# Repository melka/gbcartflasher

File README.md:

# gbcartflasher

PCB for the ATMega8515 / FT232RL based Gameboy Cart Flasher &amp; some mods to make it work easily under MacOS

## background

We needed to write a small text-based game, like Zork, for the gameboy. We wanted it to run on the original hardware and look like an original cartridge.

In order to flash a cartridge, you need to either mod an existing one by removing the ROM and replacing it with your own flash, but since the software was pretty simple, I figured I should make a PCB for a 32K flash that could be assembled easily. We had to make around 10 copies in a limited time.

One of the simplest and most used Gameboy Cart Flasher is the one designed by Kraku & Chroost. The schematics and software can be found on the [awesome website](http://www.reinerziegler.de/readplus.htm) maintained by Reiner Ziegler.

What you'll find in this repo are the eagle files ready to be sent to a fab house (I used [elecrow](https://www.elecrow.com/pcb-prototyping.html)), plus some instructions and a modified software to make it run easily on MacOS.

## BOM

Full BOM can be found on Mouser :
* [32K Cart](http://www.mouser.com/ProjectManager/ProjectDetail.aspx?AccessID=d0bee9d82e)
* [Cart Flasher](http://www.mouser.com/ProjectManager/ProjectDetail.aspx?AccessID=779e8e7766)
* [GB Connector](http://www.dx.com/p/repair-parts-replacement-gba-game-cart-slot-for-nds-lite-37787)

## notes on PCBs

The Gameboy Cartridge connector can be taken from a broken gameboy, but the easiest way to get one is to buy a Nintendo DS GBA Slot connector and [cutting some little plastic tabs](http://sudomod.com/old_forums/reply/771/) in order to get the original GB cartridges to fit.

In order to fit, the PCB for the cartridge needs to be 0.8mm thick, so be careful when ordering to check that your fab house can make it.

## programming the flasher

To program the ATmega8515, you'll need an ICSP programmer for AVR chips. I used an [USBasp](http://www.fischl.de/usbasp/) clone.

Using avrdude, fuses need to be set as low 0x1F and high 0xc9

```
avrdude -P usb -c usbasp -p ATmega8515 -qq -B 8 -U lfuse:w:0x1f:m -U hfuse:w:0xc9:m
````

I programmed my flasher using the .hex file [found here](http://www.reinerziegler.de/readplus.htm#GB_Flasher). Be careful to flash the USB version.

```
avrdude -P usb -c usbasp -p ATmega8515 -qq -B 8 -U flash:w:gbcf-fw-2.1-usb.hex
```

The firmware has been [rewritten in C in 2015 by Tauwasser](https://github.com/Tauwasser/GBCartFlasher), but I haven't tested that version personally.

## libftdi, kext and MacOS

On MacOS, when you plug the flasher, the OS loads one or more kexts to act as drivers for the hardware. Those kexts are AppleUSBFTDI and, if you installed the FTDI VCP drivers, FTDIUSBSerialDriver.kext.

The host software uses libftdi to talk to the flasher, and those kexts are locking the USB port we need.

An easy solution is to unload the kexts before launching the host software :

```
sudo kextunload /System/Library/Extensions/AppleUSBFTDI.kext/
sudo kextunload /System/Library/Extensions/FTDIUSBSerialDriver.kext/
sudo kextunload /Library/Extensions/FTDIUSBSerialDriver.kext/
```

But it's cumbersome, and I always forget that step...

Since kexts are loaded according to the USB VID / PID, we changed the VID / PID / Description of the FT232 chip using [FT_Prog](http://www.ftdichip.com/Support/Utilities.htm#FT_PROG) under Windows. Changing to those exacts values is required if you want to use the host software provided since they are hard-coded for the time being.

```
Product Description : gbcflsh
VID : 1209
PID : 6BCF
```

Those IDs are provided by the awesome [pid.codes project](http://pid.codes/).

By changing the IDs, MacOS no longer tries to load the AppleUSBFTDI & FTDIUSBSerialDriver kexts, and libftdi can do its work.

## host software

On mac, you'll need to install Qt4 & libftdi :

```
brew tap cartr/qt4
brew install cartr/qt4/qt libftdi
```

Then, in the gbcflsh_1.1_libftdi folder :

```
qmake && make
```

You should find a gbcflsh.app in the release folder.

### references
 * [jrodrigo gb cart flasher](http://www.jrodrigo.net/es/project/gameboy-cart-flasher/)

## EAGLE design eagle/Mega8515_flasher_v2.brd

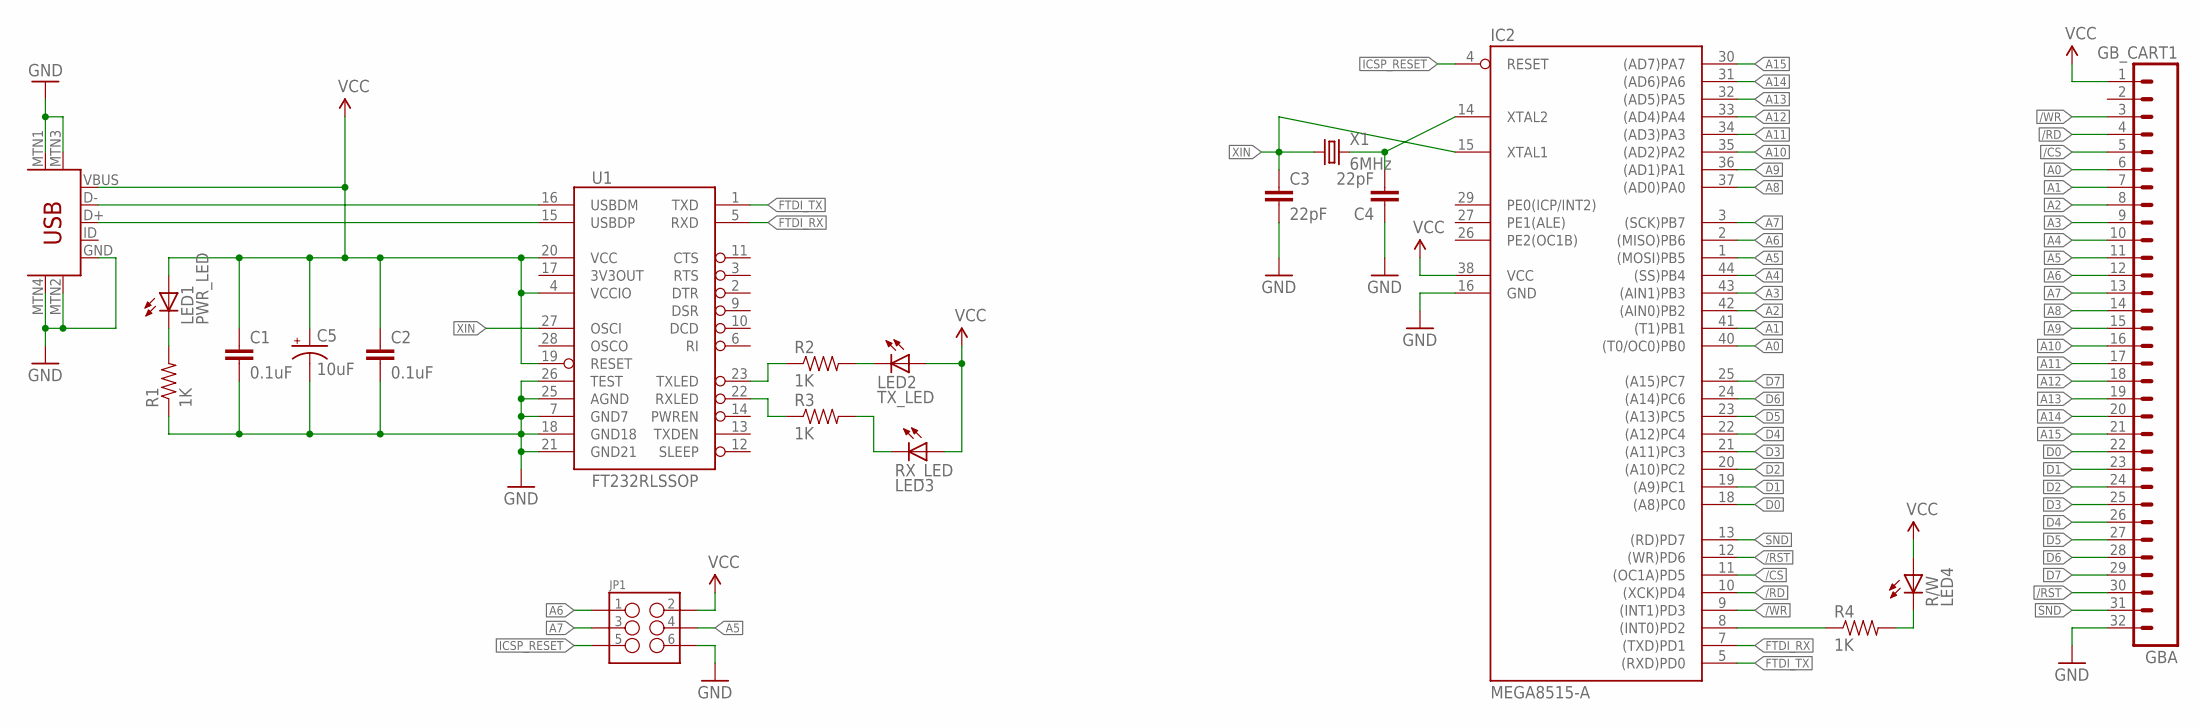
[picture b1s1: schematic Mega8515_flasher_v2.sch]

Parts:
C1, C2: 0.1uF; 1206
C3, C4: 22pF; 0805
C5: 10uF; EIA3216
GBA: GB_CART1; GB_CART_1
IC2: MEGA8515-A; TQFP44
JP1: SPARKFUN-CONNECTORS_M03X2SMT; SPARKFUN-CONNECTORS_2X3_SMT_POSTS
LED1: PWR_LED; LED-1206
LED2: TX_LED; LED-1206
R1, R2, R3, R4: 1K; 1206
R/W: LED4; LED-1206
RX_LED: LED3; LED-1206
U1: FT232RLSSOP; SSOP28DB
USB: USB-MINIB-5PIN; USB-MINIB
X1: 6MHz; SPARKFUN-FREQCTRL_CRYSTAL-SMD-11.8X5.5

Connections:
/CS: GBA.5, IC2.11 ((OC1A)PD5)
/RD: GBA.4, IC2.10 ((XCK)PD4)
/RST: GBA.30, IC2.12 ((WR)PD6)
/WR: GBA.3, IC2.9 ((INT1)PD3)
A0: GBA.6, IC2.40 ((T0/OC0)PB0)
A1: GBA.7, IC2.41 ((T1)PB1)
A2: GBA.8, IC2.42 ((AIN0)PB2)
A3: GBA.9, IC2.43 ((AIN1)PB3)
A4: GBA.10, IC2.44 ((SS)PB4)
A5: GBA.11, IC2.1 ((MOSI)PB5), JP1.4
A6: GBA.12, IC2.2 ((MISO)PB6), JP1.1
A7: GBA.13, IC2.3 ((SCK)PB7), JP1.3
A8: GBA.14, IC2.37 ((AD0)PA0)
A9: GBA.15, IC2.36 ((AD1)PA1)
A10: GBA.16, IC2.35 ((AD2)PA2)
A11: GBA.17, IC2.34 ((AD3)PA3)
A12: GBA.18, IC2.33 ((AD4)PA4)
A13: GBA.19, IC2.32 ((AD5)PA5)
A14: GBA.20, IC2.31 ((AD6)PA6)
A15: GBA.21, IC2.30 ((AD7)PA7)
D0: GBA.22, IC2.18 ((A8)PC0)
D1: GBA.23, IC2.19 ((A9)PC1)
D2: GBA.24, IC2.20 ((A10)PC2)
D3: GBA.25, IC2.21 ((A11)PC3)
D4: GBA.26, IC2.22 ((A12)PC4)
D5: GBA.27, IC2.23 ((A13)PC5)
D6: GBA.28, IC2.24 ((A14)PC6)
D7: GBA.29, IC2.25 ((A15)PC7)
FTDI_RX: IC2.7 ((TXD)PD1), U1.5 (RXD)
FTDI_TX: IC2.5 ((RXD)PD0), U1.1 (TXD)
GND: C1.2, C2.2, C3.2, C4.1, C5.C (-), GBA.32, IC2.16 (GND), JP1.6, R1.1, U1.7 (GND7), U1.18 (GND18), U1.21 (GND21), U1.25 (AGND), U1.26 (TEST), USB.GND, USB.MTN1 (MTN2), USB.MTN2 (MTN3), USB.MTN3 (MTN1), USB.MTN4
ICSP_RESET: IC2.4 (RESET), JP1.5
unnamed: C4.2, IC2.14 (XTAL2), X1.2, X1.3 (2)
unnamed: R4.2, R/W.C
unnamed: R3.2, RX_LED.C
unnamed: LED2.C, R2.2
unnamed: U1.16 (USBDM), USB.D-
unnamed: U1.15 (USBDP), USB.D+
unnamed: LED1.C, R1.2
RWLED: IC2.8 ((INT0)PD2), R4.1
RXLED: R3.1, U1.22 (RXLED)
SND: GBA.31, IC2.13 ((RD)PD7)
TXLED: R2.1, U1.23 (TXLED)
VCC: C1.1, C2.1, C5.A (+), GBA.1, IC2.38 (VCC), JP1.2, LED1.A, LED2.A, R/W.A, RX_LED.A, U1.4 (VCCIO), U1.19 (RESET), U1.20 (VCC), USB.VBUS
XIN: C3.1, IC2.15 (XTAL1), U1.27 (OSCI), X1.1, X1.4 (1)

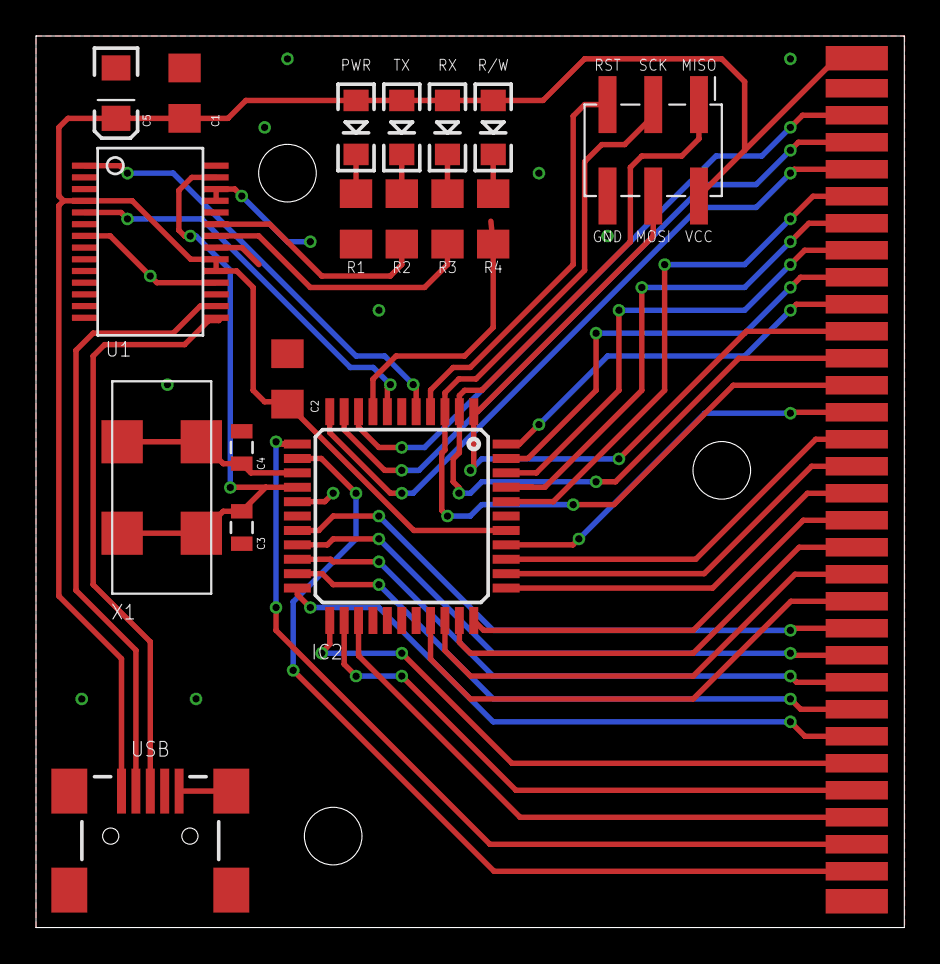
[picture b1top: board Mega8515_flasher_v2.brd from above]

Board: 2 copper layers, 48.2 x 49.5 mm, 19 parts (0 on the bottom side), 45 nets.

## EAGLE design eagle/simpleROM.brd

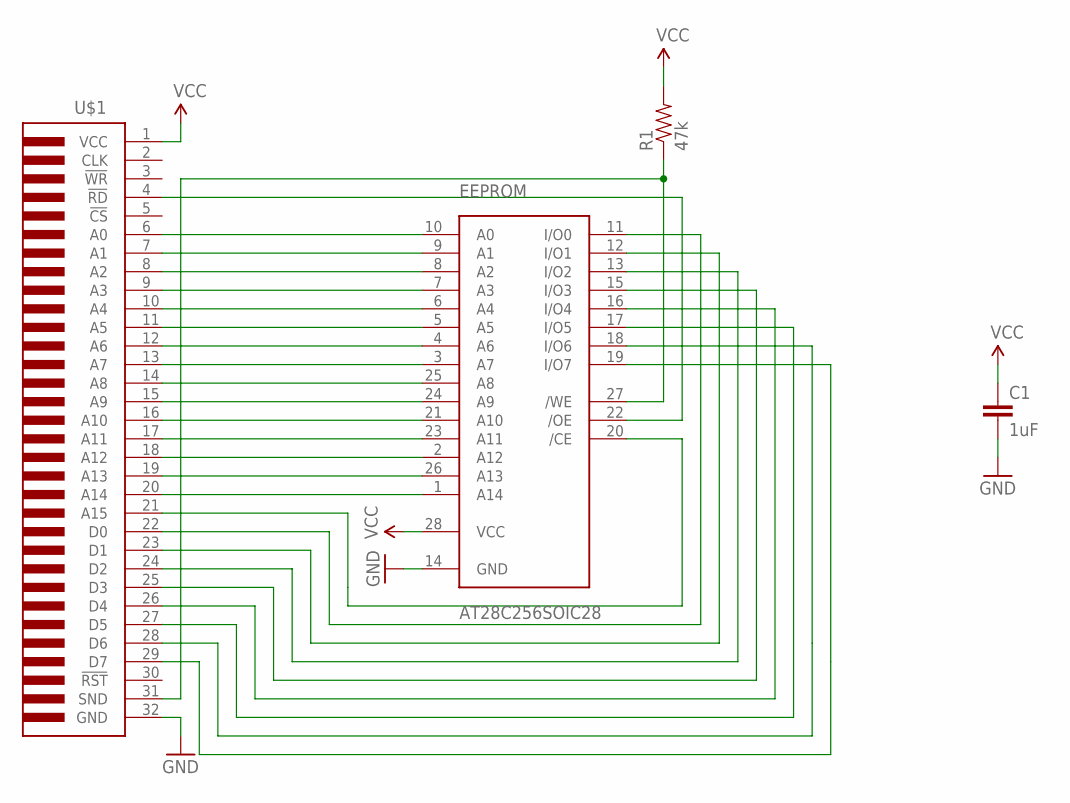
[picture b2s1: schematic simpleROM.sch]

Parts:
C1: 1uF; SPARKFUN-CAPACITORS_1206
EEPROM: AT28C256SOIC28; SO28
R1: 47k; SPARKFUN-RESISTORS_1206
U$1: GBCART-FULL; GBCART

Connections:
/CE: EEPROM.20 (/CE), U$1.21 (A15)
/OE: EEPROM.22 (/OE), U$1.4 (!RD)
/WE: EEPROM.27 (/WE), R1.1, U$1.31 (SND)
GND: C1.2, EEPROM.14 (GND), U$1.32 (GND)
unnamed: EEPROM.10 (A0), U$1.6 (A0)
unnamed: EEPROM.9 (A1), U$1.7 (A1)
unnamed: EEPROM.8 (A2), U$1.8 (A2)
unnamed: EEPROM.7 (A3), U$1.9 (A3)
unnamed: EEPROM.6 (A4), U$1.10 (A4)
unnamed: EEPROM.5 (A5), U$1.11 (A5)
unnamed: EEPROM.4 (A6), U$1.12 (A6)
unnamed: EEPROM.3 (A7), U$1.13 (A7)
unnamed: EEPROM.25 (A8), U$1.14 (A8)
unnamed: EEPROM.24 (A9), U$1.15 (A9)
unnamed: EEPROM.21 (A10), U$1.16 (A10)
unnamed: EEPROM.23 (A11), U$1.17 (A11)
unnamed: EEPROM.2 (A12), U$1.18 (A12)
unnamed: EEPROM.26 (A13), U$1.19 (A13)
unnamed: EEPROM.1 (A14), U$1.20 (A14)
unnamed: EEPROM.19 (I/O7), U$1.29 (D7)
unnamed: EEPROM.18 (I/O6), U$1.28 (D6)
unnamed: EEPROM.11 (I/O0), U$1.22 (D0)
unnamed: EEPROM.12 (I/O1), U$1.23 (D1)
unnamed: EEPROM.13 (I/O2), U$1.24 (D2)
unnamed: EEPROM.15 (I/O3), U$1.25 (D3)
unnamed: EEPROM.16 (I/O4), U$1.26 (D4)
unnamed: EEPROM.17 (I/O5), U$1.27 (D5)
VCC: C1.1, EEPROM.28 (VCC), R1.2, U$1.1 (VCC)

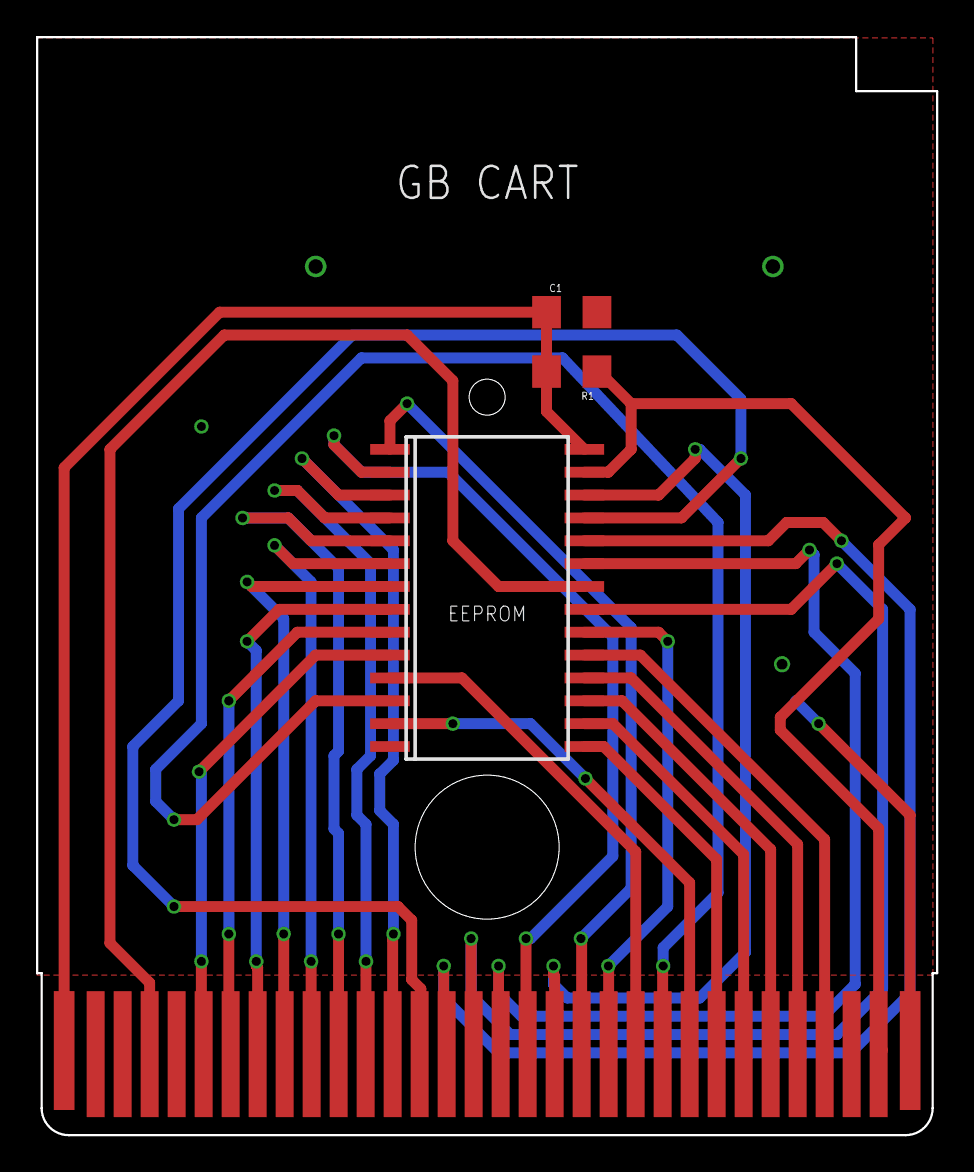
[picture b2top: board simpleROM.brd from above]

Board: 2 copper layers, 50.0 x 61.0 mm, 4 parts (0 on the bottom side), 28 nets.

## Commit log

2017-04-04 Added VID/PID/Description

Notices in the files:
parts and their libraries:
SparkFun-Connectors: Licensing: CC v3.0 Share-Alike You are welcome to use this library for commercial purposes.
